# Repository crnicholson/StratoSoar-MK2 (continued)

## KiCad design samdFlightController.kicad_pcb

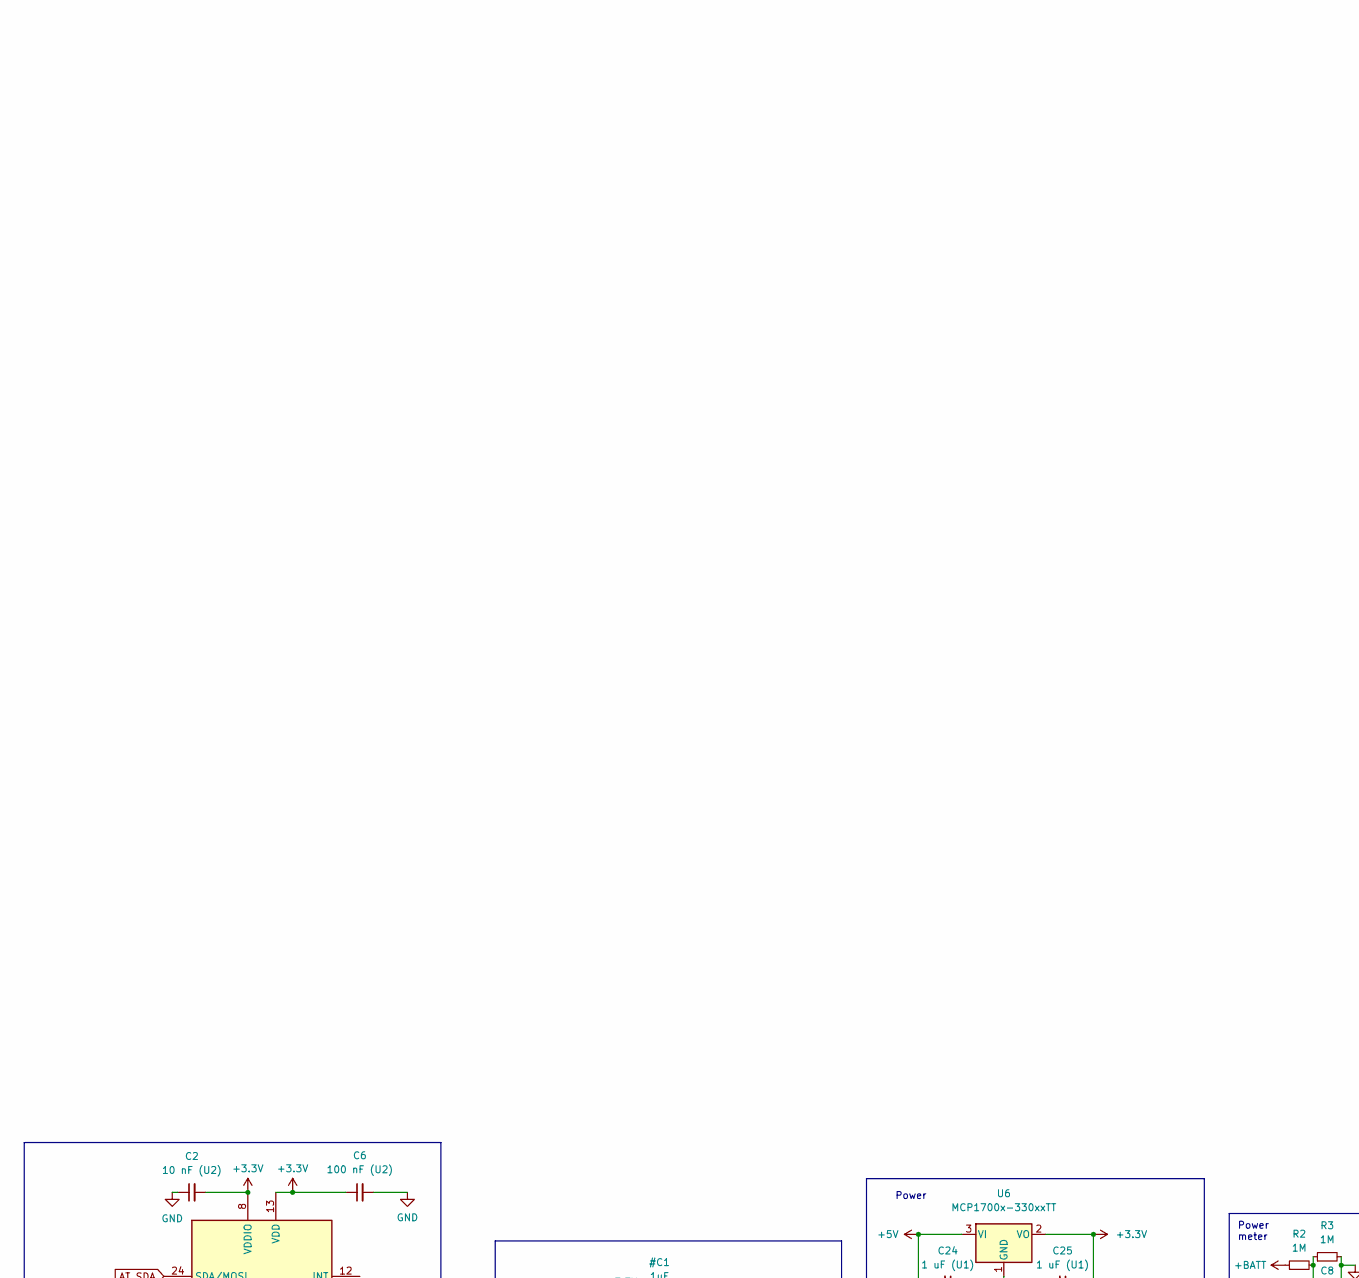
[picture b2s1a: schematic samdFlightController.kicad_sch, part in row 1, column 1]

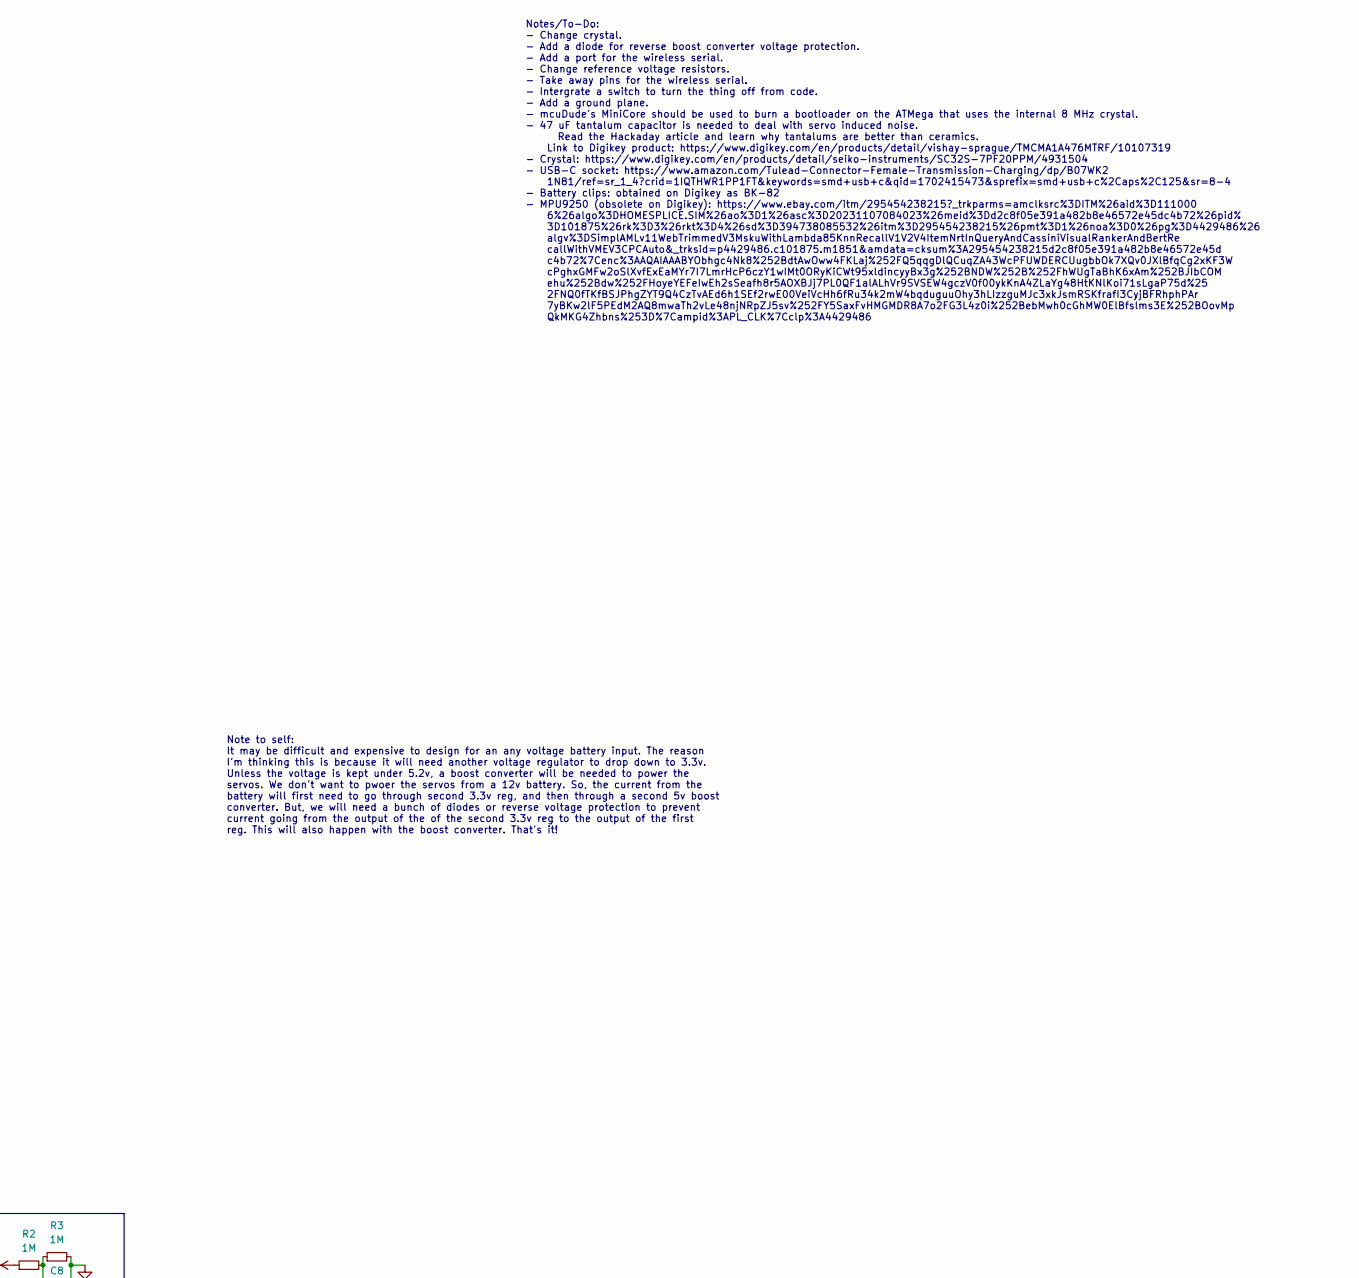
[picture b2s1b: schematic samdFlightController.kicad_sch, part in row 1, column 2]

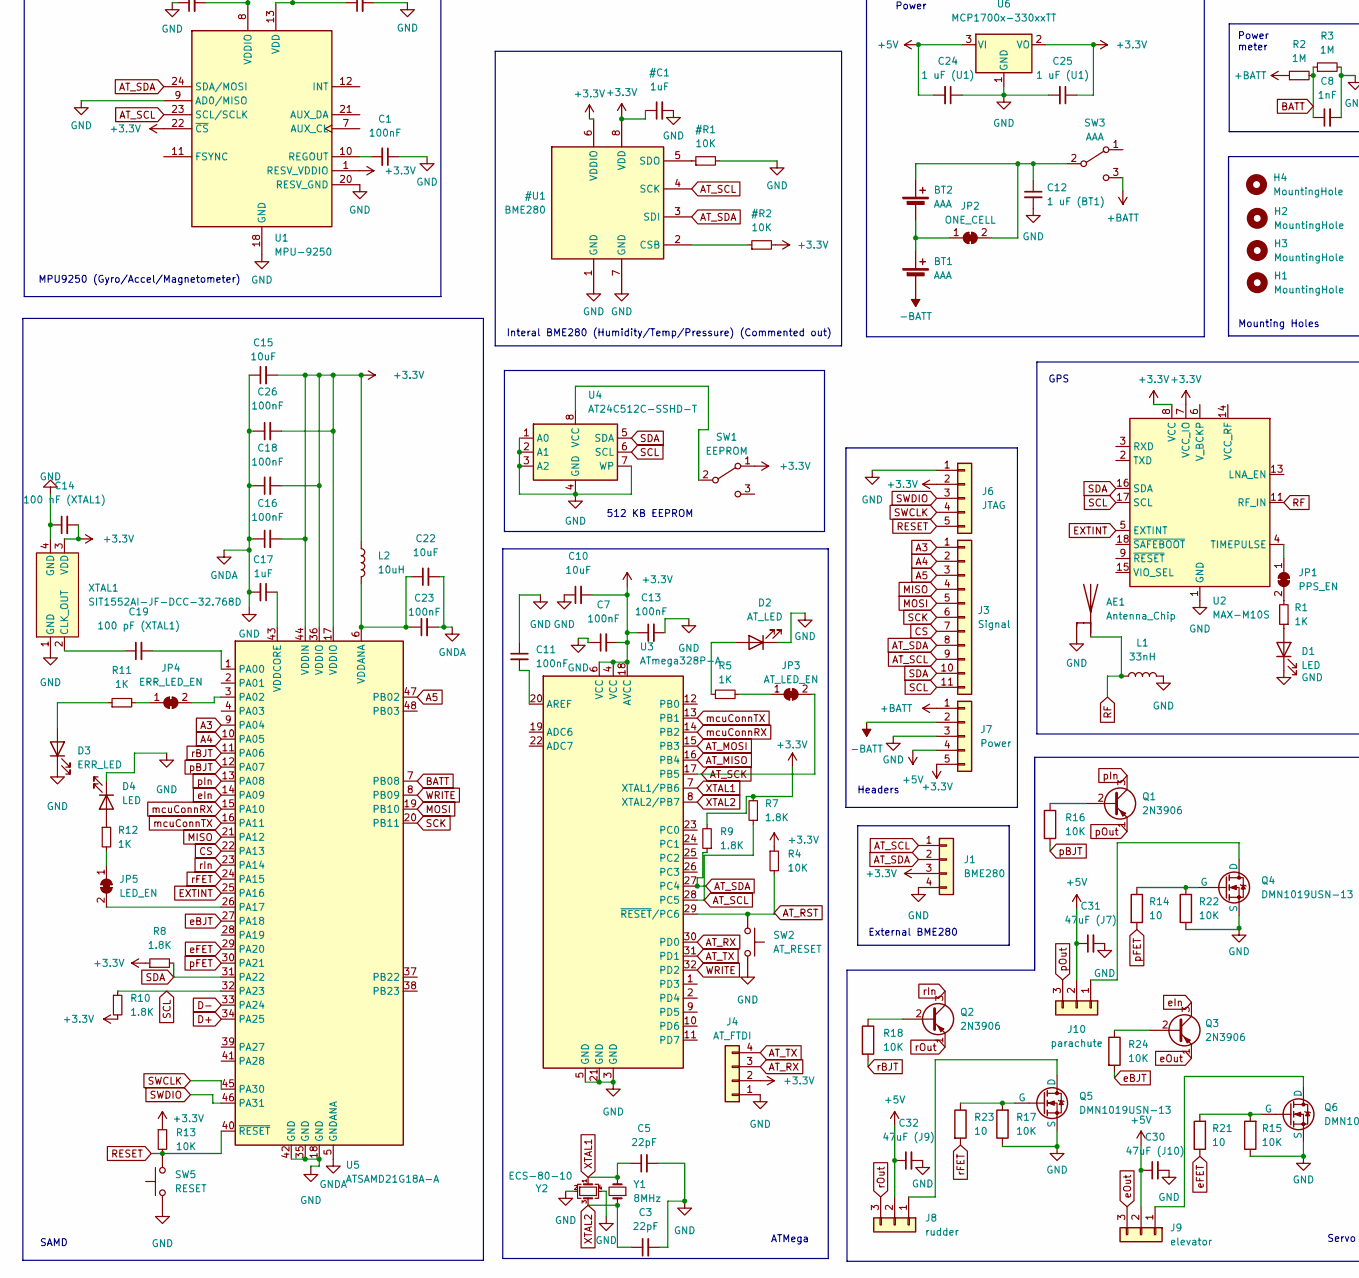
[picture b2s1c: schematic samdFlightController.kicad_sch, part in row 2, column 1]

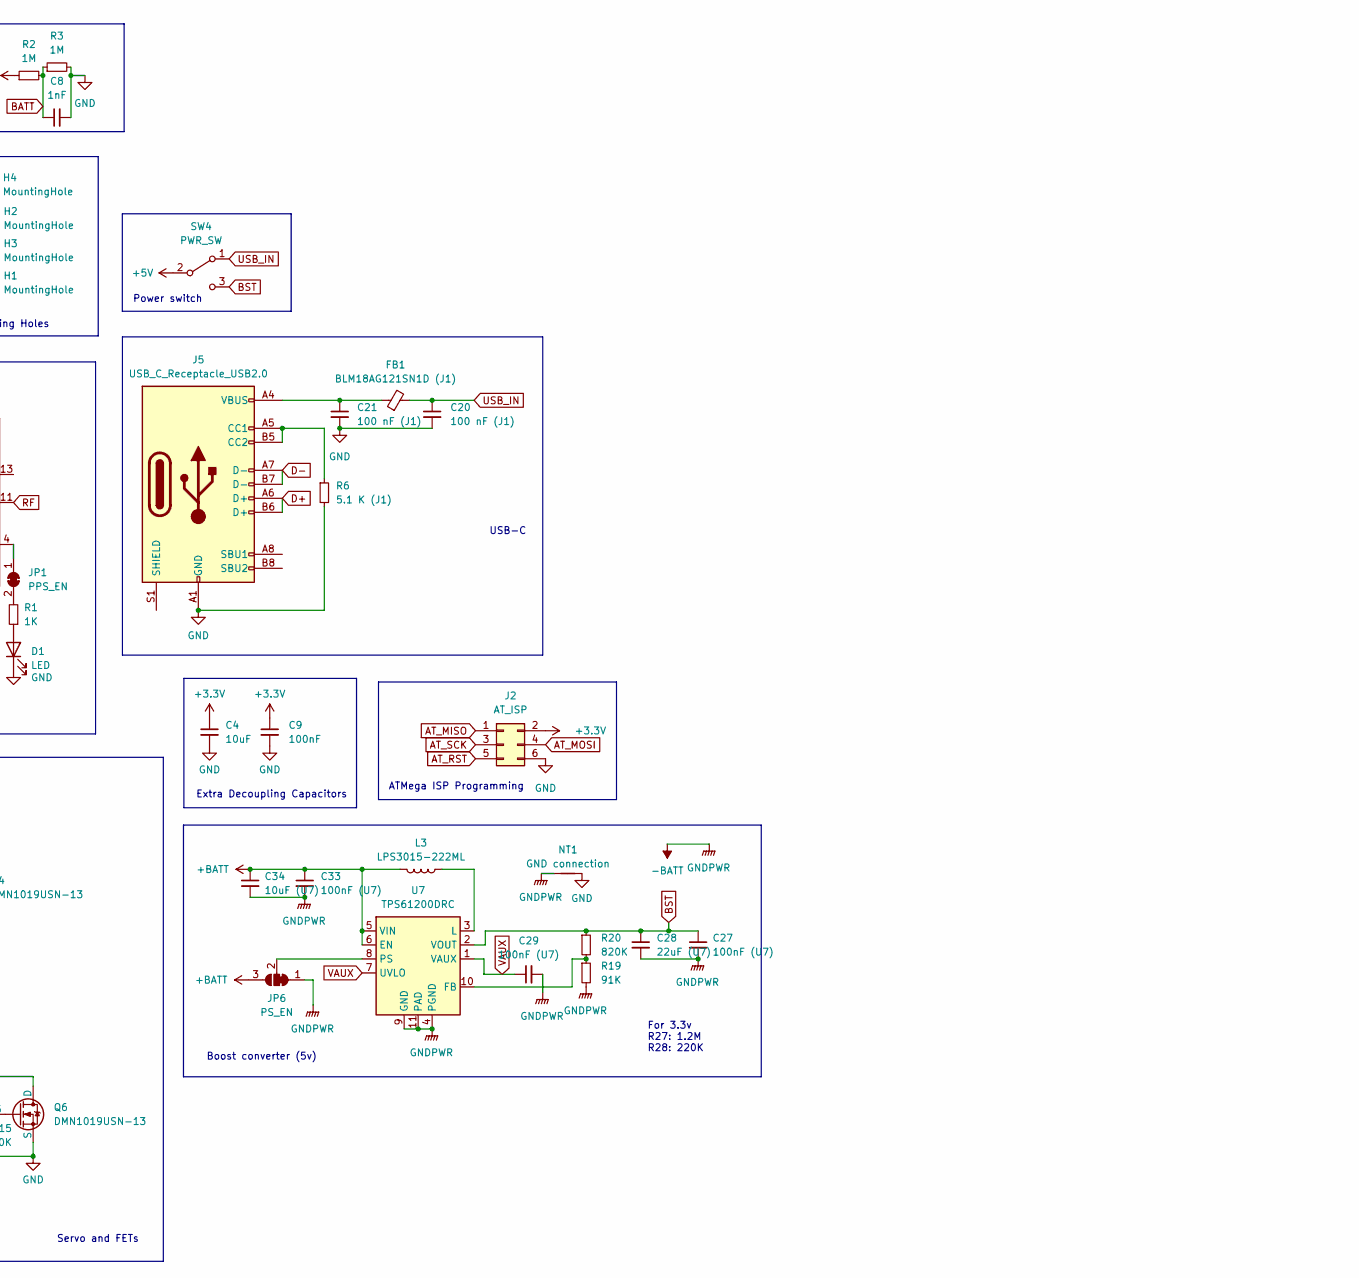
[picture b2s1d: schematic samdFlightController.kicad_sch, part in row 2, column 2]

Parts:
AE1: Antenna_Chip; RAINSUN_GPS1003
BT1, BT2: AAA; BatteryHolder_BK-82
C1, C7, C9, C11, C13, C16, C18, C23, C26: 100nF; C_0805_2012Metric_Pad1.18x1.45mm_HandSolder
C2: 10 nF (U2); C_0805_2012Metric_Pad1.18x1.45mm_HandSolder
C3, C5: 22pF; C_0805_2012Metric_Pad1.18x1.45mm_HandSolder
C4, C10, C15, C22: 10uF; C_0805_2012Metric_Pad1.18x1.45mm_HandSolder
C6: 100 nF (U2); C_0805_2012Metric_Pad1.18x1.45mm_HandSolder
C8: 1nF; C_0805_2012Metric_Pad1.18x1.45mm_HandSolder
C12: 1 uF (BT1); C_0805_2012Metric_Pad1.18x1.45mm_HandSolder
C14: 100 nF (XTAL1); C_0805_2012Metric_Pad1.18x1.45mm_HandSolder
C17: 1uF; C_0805_2012Metric_Pad1.18x1.45mm_HandSolder
C19: 100 pF (XTAL1); C_0805_2012Metric_Pad1.18x1.45mm_HandSolder
C20, C21: 100 nF (J1); C_0805_2012Metric_Pad1.18x1.45mm_HandSolder
C24, C25: 1 uF (U1); C_0805_2012Metric_Pad1.18x1.45mm_HandSolder
C27, C33: 100nF (U7); C_1206_3216Metric
C28: 22uF (U7); C_1206_3216Metric
C29: 100nF (U7); C_0805_2012Metric_Pad1.18x1.45mm_HandSolder
C30: 47uF (J10); C_1210_3225Metric
C31: 47uF (J7); C_1210_3225Metric
C32: 47uF (J9); C_1210_3225Metric
C34: 10uF (U7); C_1206_3216Metric
D1, D4: LED; LED_0805_2012Metric_Pad1.15x1.40mm_HandSolder
D2: AT_LED; LED_0805_2012Metric_Pad1.15x1.40mm_HandSolder
D3: ERR_LED; LED_0805_2012Metric_Pad1.15x1.40mm_HandSolder
FB1: BLM18AG121SN1D (J1); R_0603_1608Metric_Pad0.98x0.95mm_HandSolder
H1, H2, H3, H4: MountingHole; MountingHole_2.2mm_M2
J1: BME280; PinHeader_1x04_P2.54mm_Vertical
J2: AT_ISP; PinHeader_2x03_P2.54mm_Vertical
J3: Signal; PinHeader_1x11_P2.54mm_Vertical
J4: AT_FTDI; PinHeader_1x04_P2.54mm_Vertical
J5: USB_C_Receptacle_USB2.0; USB_C_Receptacle_GCT_USB4105-xx-A_16P_TopMnt_Horizontal
J6: JTAG; PinHeader_1x05_P2.54mm_Vertical
J7: Power; PinHeader_1x05_P2.54mm_Vertical
J8: rudder; PinHeader_1x03_P2.54mm_Vertical
J9: elevator; PinHeader_1x03_P2.54mm_Vertical
J10: parachute; PinHeader_1x03_P2.54mm_Vertical
JP1: PPS_EN; SolderJumper-2_P1.3mm_Bridged_RoundedPad1.0x1.5mm
JP2: ONE_CELL; SolderJumper-2_P1.3mm_Bridged_RoundedPad1.0x1.5mm
JP3: AT_LED_EN; SolderJumper-2_P1.3mm_Bridged_RoundedPad1.0x1.5mm
JP4: ERR_LED_EN; SolderJumper-2_P1.3mm_Bridged_RoundedPad1.0x1.5mm
JP5: LED_EN; SolderJumper-2_P1.3mm_Bridged_RoundedPad1.0x1.5mm
JP6: PS_EN; SolderJumper-3_P1.3mm_Bridged12_RoundedPad1.0x1.5mm
L1: 33nH; L_0805_2012Metric_Pad1.15x1.40mm_HandSolder
L2: 10uH; L_0805_2012Metric_Pad1.15x1.40mm_HandSolder
L3: LPS3015-222ML; IND_LPS3015
NT1: GND connection; NetTie-2_SMD_Pad2.0mm
Q1, Q2, Q3: 2N3906; SOT-23_Handsoldering
Q4, Q5, Q6: DMN1019USN-13; SC-59_Handsoldering
R1, R5, R11, R12: 1K; R_0805_2012Metric_Pad1.20x1.40mm_HandSolder
R2, R3: 1M; R_0805_2012Metric_Pad1.20x1.40mm_HandSolder
R4, R13, R15, R16, R17, R18, R22, R24: 10K; R_0805_2012Metric_Pad1.20x1.40mm_HandSolder
R6: 5.1 K (J1); R_0805_2012Metric_Pad1.20x1.40mm_HandSolder
R7, R8, R9, R10: 1.8K; R_0805_2012Metric_Pad1.20x1.40mm_HandSolder
R14, R21, R23: 10; R_0805_2012Metric_Pad1.20x1.40mm_HandSolder
R19: 91K; R_0805_2012Metric_Pad1.20x1.40mm_HandSolder
R20: 820K; R_0805_2012Metric_Pad1.20x1.40mm_HandSolder
SW1: EEPROM; SW_SPDT_PCM12
SW2: AT_RESET; SW_SPST_CK_RS282G05A3
SW3: AAA; SW_SPDT_PCM12
SW4: PWR_SW; SW_SPDT_PCM12
SW5: RESET; SW_SPST_CK_RS282G05A3
U1: MPU-9250; InvenSense_QFN-24_3x3mm_P0.4mm
U2: MAX-M10S; ublox_MAX
U3: ATmega328P-A; TQFP-32_7x7mm_P0.8mm
U4: AT24C512C-SSHD-T; SOIC-8_3.9x4.9mm_P1.27mm
U5: ATSAMD21G18A-A; TQFP-48_7x7mm_P0.5mm
U6: MCP1700x-330xxTT; SOT-89-3_Handsoldering
U7: TPS61200DRC; Texas_S-PVSON-N10_ThermalVias
XTAL1: SIT1552AI-JF-DCC-32.768D; BGA4_SiT1532_SIT
Y1: 8MHz; Crystal_HC18-U_Vertical
Y2: ECS-80-10; ECS801033CHNTR

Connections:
+5V: C24.2, C30.1, C31.1, C32.1, J7.4, J8.2, J9.2, J10.2, SW4.2 (B), U6.3 (VI)
+BATT: C33.1, C34.1, J7.1, JP6.3 (B), L3.2, R2.1, SW3.3 (C), U7.5 (VIN), U7.6 (EN)
-BATT: BT1.2 (-), C27.2, C28.2, C29.2, C33.2, C34.2, J7.2, JP6.1 (A), NT1.1, R19.2, U7.4 (PGND), U7.9 (GND), U7.11 (PAD)
A3: J3.1, U5.9 (PA04)
A4: J3.2, U5.10 (PA05)
A5: J3.3, U5.47 (PB02)
AT_MISO: J2.1, U3.16 (PB4)
AT_MOSI: J2.4, U3.15 (PB3)
AT_RST: J2.5, R4.2, SW2.1, U3.29 (~RESET/PC6)
AT_RX: J4.3, U3.30 (PD0)
AT_SCK: J2.3, JP3.2 (B), U3.17 (PB5)
AT_TX: J4.4, U3.31 (PD1)
BATT: C8.1, R2.2, R3.1, U5.7 (PB08)
BST: C27.1, C28.1, R20.1, SW4.3 (C), U7.2 (VOUT)
CS: J3.7, U5.22 (PA13)
D+: J5.A6 (D+), J5.B6 (D+), U5.34 (PA25)
D-: J5.A7 (D-), J5.B7 (D-), U5.33 (PA24)
EXTINT: U2.5 (EXTINT), U5.25 (PA16)
MISO: J3.4, U5.21 (PA12)
MOSI: J3.5, U5.19 (PB10)
unnamed: BT2.1 (+), C12.1, JP2.2 (B), SW3.2 (B)
unnamed: BT1.1 (+), BT2.2 (-), JP2.1 (A)
unnamed: C21.1, FB1.1, J5.A4 (VBUS), J5.A9 (VBUS), J5.B4 (VBUS), J5.B9 (VBUS)
unnamed: D1.2 (A), R1.1
unnamed: D2.2 (A), R5.1
unnamed: D3.2 (A), R11.1
unnamed: D4.2 (A), R12.1
unnamed: J8.1, Q5.1 (D)
unnamed: J9.1, Q6.1 (D)
unnamed: J10.1, Q4.1 (D)
unnamed: J5.A5 (CC1), J5.B5 (CC2), R6.1
unnamed: JP1.1 (A), U2.4 (TIMEPULSE)
unnamed: JP1.2 (B), R1.2
unnamed: JP3.1 (A), R5.2
unnamed: JP4.1 (A), R11.2
unnamed: JP4.2 (B), U5.3 (PA02)
unnamed: JP5.1 (A), R12.2
unnamed: JP5.2 (B), U5.26 (PA17)
unnamed: JP6.2 (C), U7.8 (PS)
unnamed: Q1.2 (B), R16.1
unnamed: Q2.2 (B), R18.1
unnamed: Q3.2 (B), R24.1
unnamed: Q4.2 (G), R14.1, R22.2
unnamed: Q5.2 (G), R17.2, R23.1
unnamed: Q6.2 (G), R15.2, R21.2
unnamed: SW1.2 (B), U4.8 (VCC)
unnamed: C1.2, U1.10 (REGOUT)
unnamed: C11.2, U3.20 (AREF)
unnamed: C19.2, U5.1 (PA00)
unnamed: C22.1, C23.1, L2.2, U5.6 (VDDANA)
unnamed: C17.1, U5.43 (VDDCORE)
unnamed: R19.1, R20.2, U7.10 (FB)
unnamed: L3.1, U7.3 (L)
unnamed: C19.1, XTAL1.2 (CLK_OUT)
RESET: J6.5, R13.2, SW5.2, U5.40 (~RESET)
RF: AE1.2 (RF), L1.1, U2.11 (RF_IN)
SCK: J3.6, U5.20 (PB11)
SCL: J3.11, R10.1, U2.17 (SCL), U4.6 (SCL), U5.32 (PA23)
SDA: J3.10, R8.2, U2.16 (SDA), U4.5 (SDA), U5.31 (PA22)
SWCLK: J6.4, U5.45 (PA30)
SWDIO: J6.3, U5.46 (PA31)
USB_IN: C20.1, FB1.2, SW4.1 (A)
VAUX: C29.1, U7.1 (VAUX), U7.7 (UVLO)
WRITE: U3.32 (PD2), U5.8 (PB09)
XTAL1: C5.1, U3.7 (XTAL1/PB6), Y1.2, Y2.1
XTAL2: C3.1, U3.8 (XTAL2/PB7), Y1.1, Y2.3
eBJT: R24.2, U5.27 (PA18)
eFET: R21.1, U5.29 (PA20)
eIn: Q3.3 (C), U5.14 (PA09)
eOut: J9.3, Q3.1 (E)
mcuConnRX: U3.14 (PB2), U5.15 (PA10)
mcuConnTX: U3.13 (PB1), U5.16 (PA11)
pBJT: R16.2, U5.12 (PA07)
pFET: R14.2, U5.30 (PA21)
pIn: Q1.3 (C), U5.13 (PA08)
pOut: J10.3, Q1.1 (E)
rBJT: R18.2, U5.11 (PA06)
rFET: R23.2, U5.24 (PA15)
rIn: Q2.3 (C), U5.23 (PA14)
rOut: J8.3, Q2.1 (E)

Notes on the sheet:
Headers
ATMega
External BME280
Power meter
ATMega ISP Programming
For 3.3v R27: 1.2M R28: 220K
Interal BME280 (Humidity/Temp/Pressure) (Commented out)
Notes/To-Do: - Change crystal. - Add a diode for reverse boost converter voltage protection. - Add a port for the wireless serial. - Change reference voltage resistors. - Take away pins for the wireless serial. - Intergrate a switch to turn the thing off from code. - Add a ground plane. - mcuDude's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
Mounting Holes
SAMD
Boost converter (5v)
USB-C
MPU9250 (Gyro/Accel/Magnetometer)
Extra Decoupling Capacitors
GPS
512 KB EEPROM
Power switch
Servo and FETs
Note to self: It may be difficult and expensive to design for an any voltage battery input. The reason I'm thinking this is because it will need another voltage regulator to drop down to 3.3v. Unless the voltage is kept under 5.2v, a boost converter will be needed to power the servos. We don't want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
Power

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
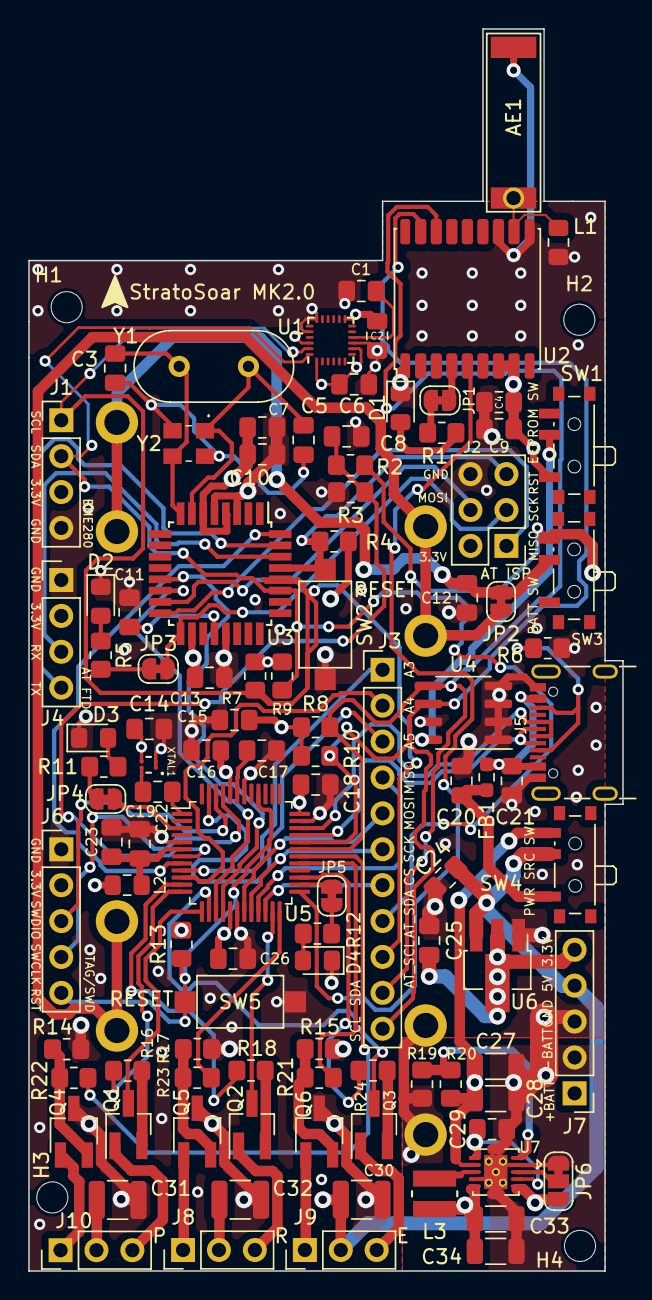
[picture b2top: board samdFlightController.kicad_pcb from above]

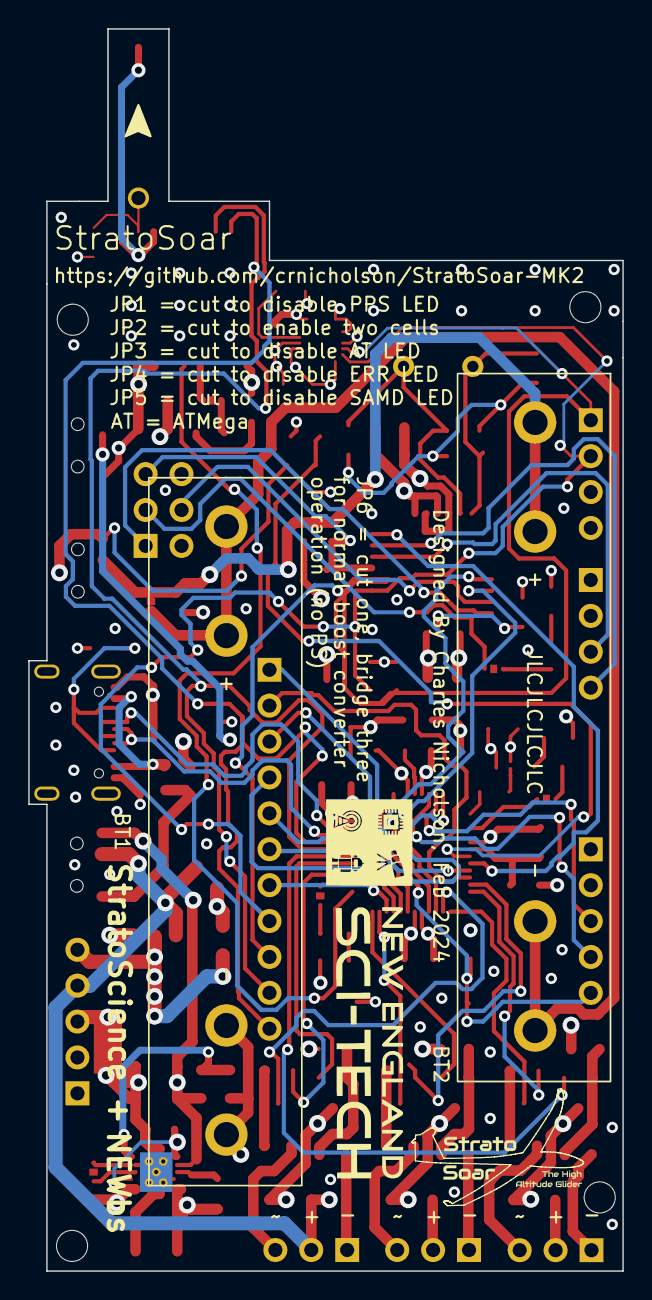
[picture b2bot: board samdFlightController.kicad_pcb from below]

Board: 4 copper layers, 42.0 x 87.9 mm, 111 parts (2 on the bottom side), 84 nets.

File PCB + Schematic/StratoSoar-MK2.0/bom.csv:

Designator,Footprint,Quantity,Value,LCSC Part #
AE1,RAINSUN_GPS1003,1,Antenna_Chip,
"BT1, BT2",BatteryHolder_BK-82,2,AAA,
"C1, C11, C13, C16, C18, C23, C26, C7, C9",0805,9,100nF,
"C10, C15, C22, C4",0805,4,10uF,
C12,0805,1,1 uF (BT1),
C14,0805,1,100 nF (XTAL1),
C17,0805,1,1uF,
C19,0805,1,100 pF (XTAL1),
C2,0805,1,10 nF (U2),
"C20, C21",0805,2,100 nF (J1),
"C24, C25",0805,2,1 uF (U1),
"C27, C33",1206,2,100nF (U7),
C28,1206,1,22uF (U7),
C29,0805,1,100nF (U7),
"C3, C5",0805,2,22pF,
C30,1210,1,47uF (J10),
C31,1210,1,47uF (J7),
C32,1210,1,47uF (J9),
C34,1206,1,10uF (U7),
C6,0805,1,100 nF (U2),
C8,0805,1,1nF,
"D1, D4",0805,2,LED,
D2,0805,1,AT_LED,
D3,0805,1,ERR_LED,
FB1,0603,1,BLM18AG121SN1D (J1),
"H1, H2, H3, H4",MountingHole_2.2mm_M2,4,MountingHole,
J1,PinHeader_1x04_P2.54mm_Vertical,1,BME280,
J10,PinHeader_1x03_P2.54mm_Vertical,1,parachute,
J2,PinHeader_2x03_P2.54mm_Vertical,1,AT_ISP,
J3,PinHeader_1x11_P2.54mm_Vertical,1,Signal,
J4,PinHeader_1x04_P2.54mm_Vertical,1,AT_FTDI,
J5,USB_C_Receptacle_GCT_USB4105-xx-A_16P_TopMnt_Horizontal,1,USB_C_Receptacle_USB2.0,
J6,PinHeader_1x05_P2.54mm_Vertical,1,JTAG,
J7,PinHeader_1x05_P2.54mm_Vertical,1,Power,
J8,PinHeader_1x03_P2.54mm_Vertical,1,rudder,
J9,PinHeader_1x03_P2.54mm_Vertical,1,elevator,
JP1,SolderJumper-2_P1.3mm_Bridged_RoundedPad1.0x1.5mm,1,PPS_EN,
JP2,SolderJumper-2_P1.3mm_Bridged_RoundedPad1.0x1.5mm,1,ONE_CELL,
JP3,SolderJumper-2_P1.3mm_Bridged_RoundedPad1.0x1.5mm,1,AT_LED_EN,
JP4,SolderJumper-2_P1.3mm_Bridged_RoundedPad1.0x1.5mm,1,ERR_LED_EN,
JP5,SolderJumper-2_P1.3mm_Bridged_RoundedPad1.0x1.5mm,1,LED_EN,
JP6,SolderJumper-3_P1.3mm_Bridged12_RoundedPad1.0x1.5mm,1,PS_EN,
L1,0805,1,33nH,
L2,0805,1,10uH,
L3,IND_LPS3015,1,LPS3015-222ML ,
"Q1, Q2, Q3",SOT-23_Handsoldering,3,2N3906,
"Q4, Q5, Q6",SC-59_Handsoldering,3,DMN1019USN-13,
"R1, R11, R12, R5",0805,4,1K,
"R10, R7, R8, R9",0805,4,1.8K,
"R13, R15, R16, R17, R18, R22, R24, R4",0805,8,10K,
"R14, R21, R23",0805,3,10,
R19,0805,1,91K,
"R2, R3",0805,2,1M,
R20,0805,1,820K,
R6,0805,1,5.1 K (J1),
SW1,SW_SPDT_PCM12,1,EEPROM,
SW2,SW_SPST_CK_RS282G05A3,1,AT_RESET,
SW3,SW_SPDT_PCM12,1,AAA,
SW4,SW_SPDT_PCM12,1,PWR_SW,
SW5,SW_SPST_CK_RS282G05A3,1,RESET,
U1,InvenSense_QFN-24_3x3mm_P0.4mm,1,MPU-9250,
U2,ublox_MAX,1,MAX-M10S,
U3,TQFP-32_7x7mm_P0.8mm,1,ATmega328P-A,
U4,SOIC-8_3.9x4.9mm_P1.27mm,1,AT24C512C-SSHD-T,
U5,TQFP-48_7x7mm_P0.5mm,1,ATSAMD21G18A-A,
U6,SOT-89-3_Handsoldering,1,MCP1700x-330xxTT,
U7,Texas_S-PVSON-N10_ThermalVias,1,TPS61200DRC,
XTAL1,BGA4_SiT1532_SIT,1,SIT1552AI-JF-DCC-32.768D,
Y1,Crystal_HC18-U_Vertical,1,8MHz,
Y2,ECS801033CHNTR,1,ECS-80-10,

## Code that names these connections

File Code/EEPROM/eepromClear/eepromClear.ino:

/*
eepromClear.ino, part of StratoSoar MK2, for an autonomous glider.
Copyright (C) 2024 Charles Nicholson

This program is free software: you can redistribute it and/or modify
it under the terms of the GNU General Public License as published by
the Free Software Foundation, either version 3 of the License, or
(at your option) any later version.

This program is distributed in the hope that it will be useful,
but WITHOUT ANY WARRANTY; without even the implied warranty of
MERCHANTABILITY or FITNESS FOR A PARTICULAR PURPOSE.  See the
GNU General Public License for more details.

You should have received a copy of the GNU General Public License
along with this program.  If not, see <https://www.gnu.org/licenses/>.
*/

// Simply upload this code to the main MCU (SAMD21G18A) to clear the EEPROM data.

// IMPORTANT: copy and paste pin definitions from main settings.h if you've changed the pins and aren't using the PCB.
// Stupid Arduino doesn't allow for relative paths...

#define RUDDER_PIN 2        // Hardware pin 23. Servo signal pin that attaches to "input" of BJT.
#define ELEVATOR_PIN 3      // Hardware pin 14. Servo signal pin that attaches to "input" of BJT.
#define PARACHUTE_PIN 4     // Hardware pin 13. Servo signal pin that attaches to "input" of BJT.
#define RUDDER_FET 5        // Hardware pin 24. Pin that attaches to switching part of FET. This allows the servo to be turned on.
#define ELEVATOR_FET 6      // Hardware pin 29. Pin that attaches to switching part of FET. This allows the servo to be turned on.
#define PARACHUTE_FET 7     // Hardware pin 30. Pin that attaches to switching part of FET. This allows the servo to be turned on.
#define RUDDER_BJT 8        // Hardware pin 11. Pin that attaches to switching part of BJT. This allows the signal to pass to the servo.
#define PARACHUTE_BJT 9     // Hardware pin 12. Pin that attaches to switching part of BJT. This allows the signal to pass to the servo.
#define ELEVATOR_BJT 10     // Hardware pin 27. Pin that attaches to switching part of BJT. This allows the signal to pass to the servo.
#define WAKEUP_PIN 11       // Hardware pin 25. Pin that attaches to the EXTINT of ublox module.
#define FALSE_WAKEUP_PIN 12 // Hardware pin 28. Pin that is used for the interrupt that puts the glider into deep sleep. Do not connect anything.
#define LED 13              // Hardware pin 26. Pin that is connected to the main green LED.
#define ERR_LED A0          // Hardware pin 3. Pin that connects ot the red error LED.
#define BAT_VOLTAGE_PIN A1  // Hardware pin 7. Pin for battery voltage measurement.
#define WRITE_PIN A2        // Hardware pin 8. Pin that is driven high to receive SerialUSB data from the ATMega.
// #define GPIO A3 // Hardware pin 9. Unused GPIO on autopilot.
#define WIRELESS_RX A4 // Hardware pin 10. Pin that connects to the HCO5. More info in the docs.
#define WIRELESS_TX A5 // Hardware pin 47. Pin that connects to the HCO5. More info in the docs.

// Other settings.
#define SERIAL_BAUD_RATE 115200 // Serial monitor baud rate.

#include "SparkFun_External_EEPROM.h" // Click here to get the library: http://librarymanager/All#SparkFun_External_EEPROM
#include <Wire.h>

long startTimer, endTimer, length, average;

ExternalEEPROM myMem;

void setup() {
  pinMode(LED, OUTPUT);
  pinMode(ERR_LED, OUTPUT);
  pinMode(RUDDER_BJT, OUTPUT);
  pinMode(ELEVATOR_BJT, OUTPUT);
  pinMode(PARACHUTE_BJT, OUTPUT);
  pinMode(RUDDER_FET, OUTPUT);
  pinMode(ELEVATOR_FET, OUTPUT);
  pinMode(PARACHUTE_FET, OUTPUT);
  pinMode(WAKEUP_PIN, OUTPUT);
  pinMode(FALSE_WAKEUP_PIN, INPUT);
  pinMode(BAT_VOLTAGE_PIN, INPUT);
  pinMode(WRITE_PIN, OUTPUT);
  digitalWrite(LED, LOW);
  digitalWrite(ERR_LED, LOW);
  digitalWrite(RUDDER_BJT, HIGH);
  digitalWrite(ELEVATOR_BJT, HIGH);
  digitalWrite(PARACHUTE_BJT, HIGH);
  digitalWrite(RUDDER_FET, LOW);
  digitalWrite(ELEVATOR_FET, LOW);
  digitalWrite(PARACHUTE_FET, LOW);
  digitalWrite(WAKEUP_PIN, LOW);
  digitalWrite(WRITE_PIN, LOW);

  Wire.begin();

  blink(LED);

  SerialUSB.begin(SERIAL_BAUD_RATE);
  while (!SerialUSB)
    ;

  delay(5000);

  SerialUSB.println("StratoSoar MK2.x EEPROM clearer.");

  myMem.setMemoryType(512); // Valid types: 0, 1, 2, 4, 8, 16, 32, 64, 128, 256, 512, 1025, 2048

  if (myMem.begin() == false) {
    SerialUSB.println("No EEPROM detected. Freezing sketch.");
    while (1)
      blink(ERR_LED);
  }

  SerialUSB.println("EEPROM detected!");
  SerialUSB.print("EEPROM size in bytes: ");
  length = myMem.length();
  SerialUSB.println(length);
  SerialUSB.println("Erasing EEPROM, should take ~10 seconds.");
  startTimer = millis();
  myMem.erase();
  endTimer = millis();
  SerialUSB.print("Done erasing. Time took in milliseconds: ");
  SerialUSB.println(endTimer - startTimer);
  SerialUSB.println("Testing write time.");
  average = myMem.detectWriteTimeMs(10);
  SerialUSB.print("Average write time in milliseconds: ");
  SerialUSB.println(average);
  SerialUSB.println("All done!");
}

void loop() {
}

void blink(int pin) {
  digitalWrite(pin, HIGH);
  delay(500);
  digitalWrite(pin, LOW);
  delay(500);
  digitalWrite(pin, HIGH);
  delay(500);
  digitalWrite(pin, LOW);
  delay(500);
}

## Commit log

2023-10-24 Create LICENSE
2023-10-24 Rename vars.h to autopilot.v3.1/vars.h
2023-10-24 Rename settings.h to autopilot.v3.1/settings.h
2023-10-24 Rename autopilot.v3.1/autopilot.v3.1.ino to Code/autopilot.v3.1/autopilot.v3.1.ino
2023-10-24 Rename autopilot.v3.1/settings.h to Code/autopilot.v3.1/settings.h
2023-10-24 Rename autopilot.v3.1/vars.h to Code/autopilot.v3.1/vars.h
2023-10-24 Rename Code/autopilot.v3.1/autopilot.v3.1.ino to Code/Autopilots/autopilot.v3.1/autopilot.v3.1.ino
2023-10-24 Rename Code/autopilot.v3.1/settings.h to Code/Autopilots/autopilot.v3.1/settings.h
2023-10-24 Rename Code/autopilot.v3.1/vars.h to Code/Autopilots/autopilot.v3.1/vars.h
2023-10-24 Rename Code/autopilotIMU.v3.1/autopilotIMU.v3.1.ino to Code/Autopilots/autopilotIMU.v3.1/autopilotIMU.v3.1.ino
2023-12-19 Delete
2023-12-19 Update IMU
2023-12-24 Major update
2023-12-24 Update EEPROM
2024-01-13 Finally doing work again...
2024-02-08 Add I2C scan and warning
2024-02-21 Update sleep time
2024-02-21 More sleep time settings
2024-02-23 Rename stratoSoarLogo.svg to Media/stratoSoarLogo.svg
2024-02-23 Rename nestPCBLogo.png to Media/nestPCBLogo.png
2024-02-23 Rename stratoSoarLogo.png to Media/stratoSoarLogo.png
2024-02-23 Rename samdFlightController.kicad_pcb to PCB + Schematic/samdFlightController.kicad_pcb
2024-02-23 Rename samdFlightController.kicad_pro to PCB + Schematic/samdFlightController.kicad_pro
2024-02-23 Rename samdFlightController.kicad_sch to PCB + Schematic/samdFlightController.kicad_sch
2024-02-23 Rename glider v33.f3z to 3D Files/glider v33.f3z
2024-02-23 Rename partsForGlider v4.stl to 3D Files/partsForGlider v4.stl
2024-02-25 I wrote some docs!
2024-02-27 Update LICENSE
2024-02-27 Create DOCS-LICENSE
2024-02-29 Update and rename LICENSE to SOFTWARE-LICENSE
2024-02-29 Rename SOFTWARE-LICENSE to Code/SOFTWARE-LICENSE
2024-02-29 Rename MEDIA-LICENSE.MD to MEDIA-LICENSE
2024-02-29 Update and rename HARDWARE-LICENSE.MD to HARDWARE-LICENSE
2024-02-29 Create 3D-LICENSE
2024-03-02 Fix typo
2024-03-04 Add EEPROM functions
2024-03-04 EEPROM
2024-03-17 Update EEPROM, sleep
2024-03-19 Test
2024-03-19 test 2
2024-03-23 Update gitignore
2024-03-23 Add images
2024-03-23 README
2024-03-23 Update MD
2024-03-25 Update IMU calibration
2024-04-01 Update file format
2024-04-01 Got default args working
2024-04-02 Update utils
2024-04-10 Got servos working
2024-04-14 Update blink
2024-04-16 Make EEPROM work
2024-04-17 Fix EEPROM
2024-04-17 Update EEPROM (again)
2024-04-17 EEPROM!
2024-04-17 Get EEPROM and everything working!
2024-04-20 Finish new PCB
2024-04-20 Update data output
2024-04-21 Update servo
2024-05-06 PCB, Code
2024-05-06 Fix minor issue with fast update period
2024-05-06 Fix fast update period
2024-05-07 Fix some other bugs!
2024-05-10 Add 3D files
2024-05-20 Update serial
2024-05-23 Update GPS
2024-05-24 EEPROM updates
2024-05-25 Edit README
2024-05-25 Test table
2024-05-25 Update table
2024-05-25 Update table to save space
2024-06-17 Made code easier to read, added falling detection.
2024-06-17 Cleaned up 3D files
2024-06-17 Working on a fix
2024-06-18 3D files
2024-06-18 I think if the dropping detection working.
2024-06-18 Cleaning up code and starting to make a high level description.
2024-06-29 Finishing touches before launch
2024-08-14 Flight changes
2024-08-16 2D plotting!
2024-08-16 3D plotting
2024-08-16 Plotting distasnce traveled
2024-08-16 KML!
2024-08-16 KML warping
2024-08-24 Slideshow
